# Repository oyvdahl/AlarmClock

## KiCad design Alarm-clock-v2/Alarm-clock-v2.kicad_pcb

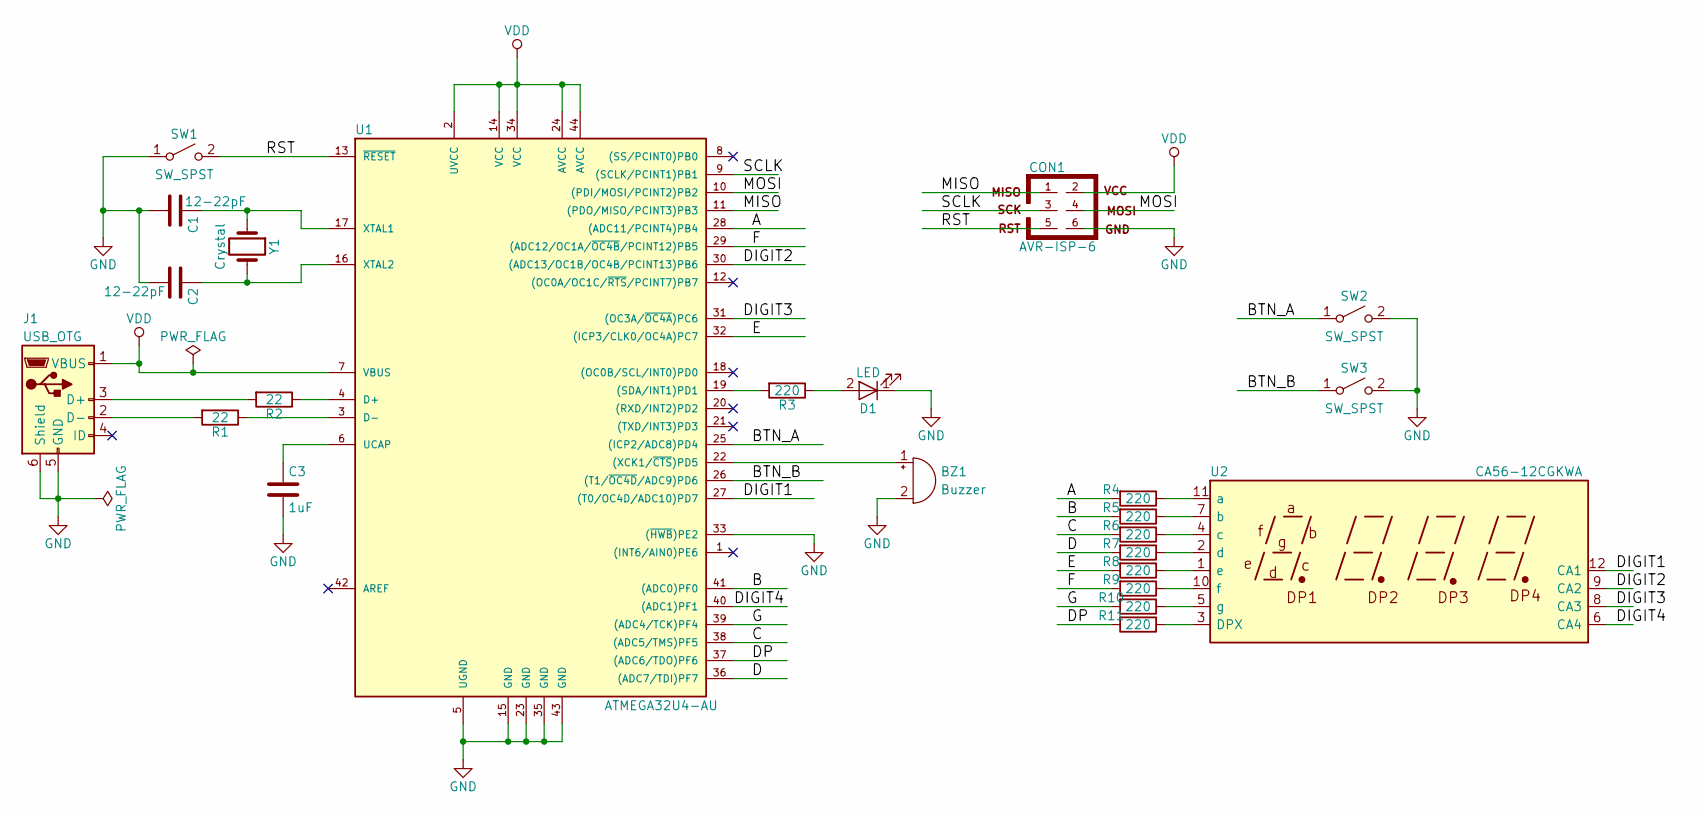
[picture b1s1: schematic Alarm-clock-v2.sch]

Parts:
BZ1: Buzzer; BUZZER
C1, C2: 12-22pF; C_0805
C3: 1uF; C_1206
CON1: AVR-ISP-6; Pin_Header_Straight_2x03_Pitch2.54mm_SMD
D1: LED; LED_1206
J1: USB_OTG; USB_Micro-B_Molex_47346-0001
R1, R2: 22; R_0805
R3, R4, R5, R6, R7, R8, R9, R10, R11: 220; R_0805
SW1, SW2, SW3: SW_SPST; SW_PUSH_6mm
U1: ATMEGA32U4-AU; TQFP-44_10x10mm_Pitch0.8mm
U2: CA56-12CGKWA
Y1: Crystal; Crystal_SMD_HC49-SD_HandSoldering

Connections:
/A: R4.2, U1.28 ((ADC11/PCINT4)PB4)
/B: R5.2, U1.41 ((ADC0)PF0)
/BTN_A: SW2.1 (A), U1.25 ((ICP2/ADC8)PD4)
/BTN_B: SW3.1 (A), U1.26 ((T1/~OC4D~/ADC9)PD6)
/C: R6.2, U1.38 ((ADC5/TMS)PF5)
/D: R7.2, U1.36 ((ADC7/TDI)PF7)
/DIGIT1: U1.27 ((T0/OC4D/ADC10)PD7), U2.12 (CA1)
/DIGIT2: U1.30 ((ADC13/OC1B/OC4B/PCINT13)PB6), U2.9 (CA2)
/DIGIT3: U1.31 ((OC3A/~OC4A~)PC6), U2.8 (CA3)
/DIGIT4: U1.40 ((ADC1)PF1), U2.6 (CA4)
/DP: R11.2, U1.37 ((ADC6/TDO)PF6)
/E: R8.2, U1.32 ((ICP3/CLK0/OC4A)PC7)
/F: R9.2, U1.29 ((ADC12/OC1A/~OC4B~/PCINT12)PB5)
/G: R10.2, U1.39 ((ADC4/TCK)PF4)
/MISO: CON1.1, U1.11 ((PDO/MISO/PCINT3)PB3)
/MOSI: CON1.4, U1.10 ((PDI/MOSI/PCINT2)PB2)
/RST: CON1.5, SW1.2 (B), U1.13 (~RESET~)
/SCLK: CON1.3, U1.9 ((SCLK/PCINT1)PB1)
GND: BZ1.2 (+), C1.2, C2.2, C3.2, CON1.6, D1.1 (K), J1.5 (GND), J1.6 (Shield), SW1.1 (A), SW2.2 (B), SW3.2 (B), U1.5 (UGND), U1.15 (GND), U1.23 (GND), U1.33 ((~HWB~)PE2), U1.35 (GND), U1.43 (GND)
unnamed: BZ1.1 (-), U1.22 ((XCK1/~CTS~)PD5)
unnamed: C1.1, U1.17 (XTAL1), Y1.1
unnamed: C2.1, U1.16 (XTAL2), Y1.2
unnamed: C3.1, U1.6 (UCAP)
unnamed: D1.2 (A), R3.1
unnamed: J1.2 (D-), R1.2
unnamed: J1.3 (D+), R2.2
unnamed: R1.1, U1.3 (D-)
unnamed: R2.1, U1.4 (D+)
unnamed: R3.2, U1.19 ((SDA/INT1)PD1)
unnamed: R4.1, U2.11 (a)
unnamed: R5.1, U2.7 (b)
unnamed: R6.1, U2.4 (c)
unnamed: R7.1, U2.2 (d)
unnamed: R8.1, U2.1 (e)
unnamed: R9.1, U2.10 (f)
unnamed: R10.1, U2.5 (g)
unnamed: R11.1, U2.3 (DPX)
VDD: CON1.2, J1.1 (VBUS), U1.2 (UVCC), U1.7 (VBUS), U1.14 (VCC), U1.24 (AVCC), U1.34 (VCC), U1.44 (AVCC)

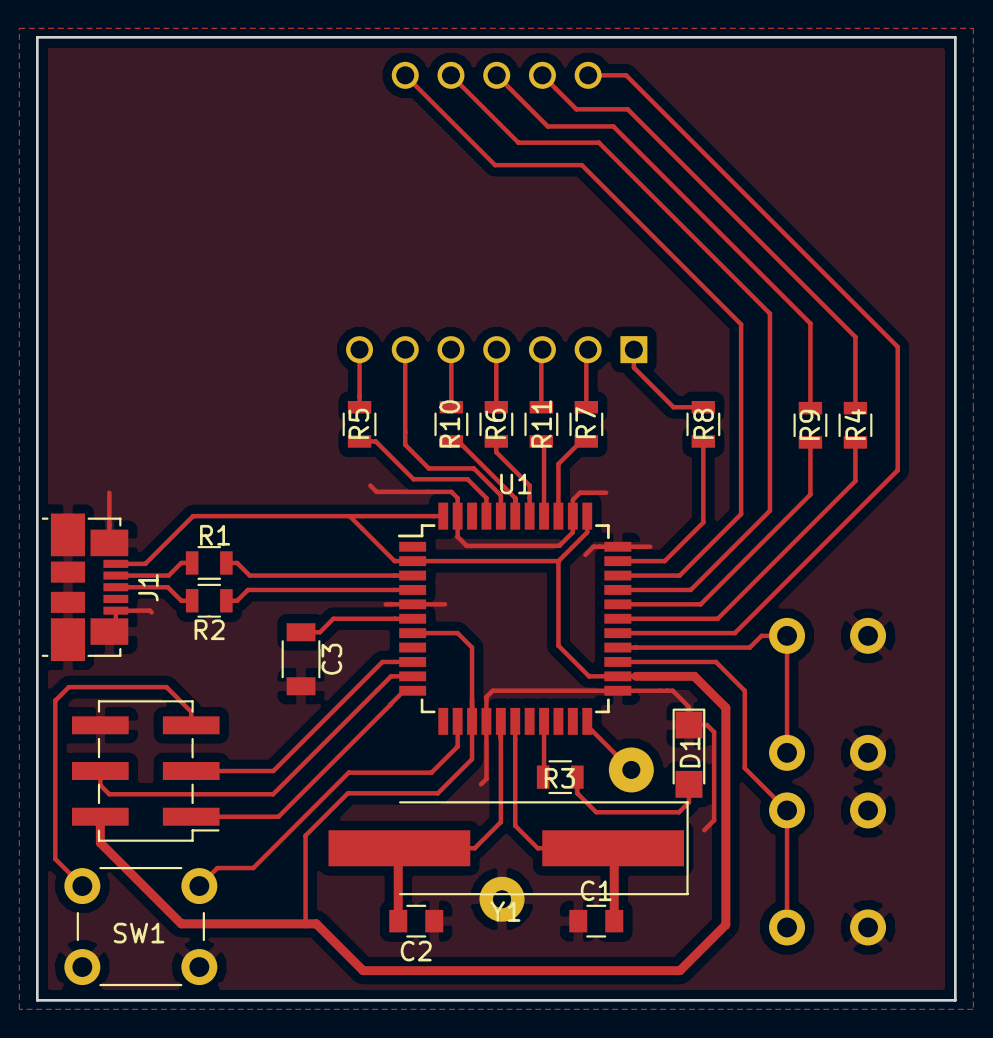
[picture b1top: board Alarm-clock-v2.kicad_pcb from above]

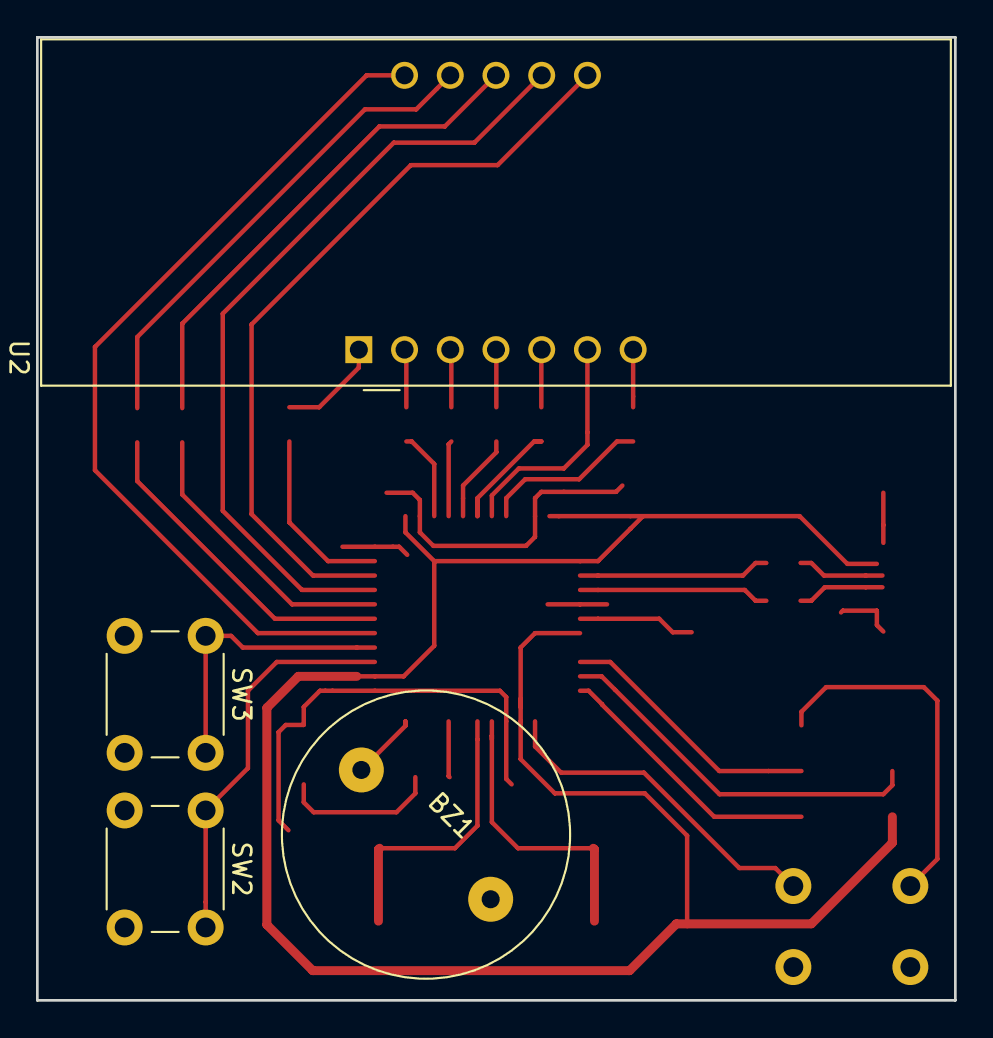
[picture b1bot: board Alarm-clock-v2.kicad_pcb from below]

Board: 2 copper layers, 51.0 x 53.5 mm, 24 parts (4 on the bottom side), 38 nets.

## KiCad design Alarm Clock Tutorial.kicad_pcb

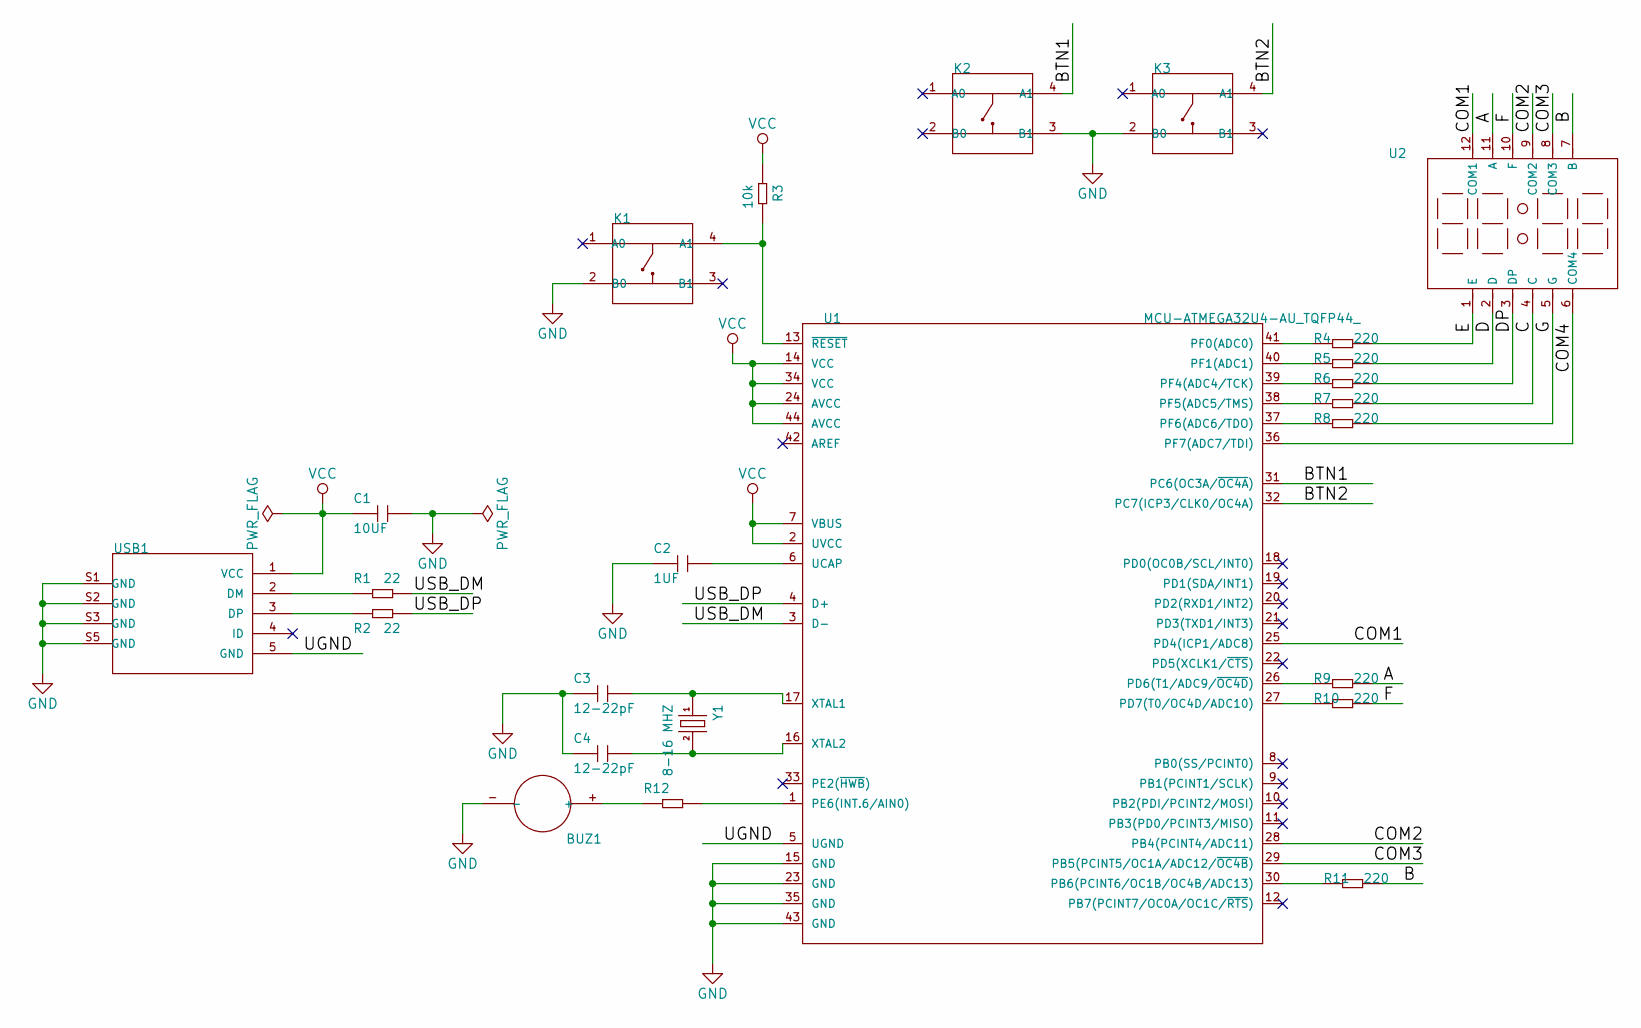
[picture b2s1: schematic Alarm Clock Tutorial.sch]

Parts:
BUZ1: DIP-BUZZER-3V_KS-12065D03YA_; BZ2-7.6-D12.0XH6.5MM; MPN KS-12065D03YA
C1: 10UF; C1206; MPN CC1206KKX5R8BB106
C2: 1UF; C0805; MPN CC0805KKX7R8BB105
C3, C4: 12-22pF; CERAMIC-2.54
K1, K2, K3: DIP-SWITCH-TACTILE-SPST-NO_TS-1109_4P-D6.0MM_; SW4-6.0X6.0X5.0MM
R1, R2: 22; R0805; MPN RC0805JR-0722RL
R3: 10k; R0402; MPN RC0402FR-0710KL
R4, R5, R6, R7, R8, R9, R10, R11: 220; R0805; MPN RC0805JR-07220RL
R12: DIP-RES-100R-5%-1_4W_PR-D2.3XL6.5MM_; PR-D2.3XL6.5MM; MPN FHCFR-1_4W-101J
U1: MCU-ATMEGA32U4-AU_TQFP44_; TQFP44-0.8-9.6X9.6MM; MPN ATMEGA32U4
U2: LED-4-BETY-7-SEG_2X7P-30X14MM_; LCD12-2.54-30.0X14.0X7.3MM; MPN LDQ-N3606RI
USB1: MICRO-USB-SMD-B-_10118193-0001LF_; MICRO-USB5+6P-SMD-0.65-B; MPN 10118193-0001LF
Y1: 8-16 MHZ; HC49US

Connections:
/A: R9.2, U2.11 (A)
/B: R11.2, U2.7 (B)
/BTN1: K2.4 (A1), U1.31 (PC6(OC3A/~OC4A))
/BTN2: K3.4 (A1), U1.32 (PC7(ICP3/CLK0/OC4A))
/C: R7.2, U2.4 (C)
/COM1: U1.25 (PD4(ICP1/ADC8)), U2.12 (COM1)
/COM2: U1.28 (PB4(PCINT4/ADC11)), U2.9 (COM2)
/COM3: U1.29 (PB5(PCINT5/OC1A/ADC12/~OC4B)), U2.8 (COM3)
/COM4: U1.36 (PF7(ADC7/TDI)), U2.6 (COM4)
/D: R5.2, U2.2 (D)
/DP: R6.2, U2.3 (DP)
/E: R4.2, U2.1 (E)
/F: R10.2, U2.10 (F)
/G: R8.2, U2.5 (G)
/UGND: U1.5 (UGND), USB1.5 (GND)
/USB_DM: R1.2, U1.3 (D-)
/USB_DP: R2.2, U1.4 (D+)
GND: BUZ1.-, C1.2, C2.1, C3.1, C4.1, K1.2 (B0), K2.3 (B1), K3.2 (B0), U1.15 (GND), U1.23 (GND), U1.35 (GND), U1.43 (GND), USB1.S1 (GND), USB1.S2 (GND), USB1.S3 (GND), USB1.S4 (GND), USB1.S5 (GND), USB1.S6 (GND)
unnamed: BUZ1.+, R12.1
unnamed: C2.2, U1.6 (UCAP)
unnamed: C3.2, U1.17 (XTAL1), Y1.1
unnamed: C4.2, U1.16 (XTAL2), Y1.2
unnamed: K1.4 (A1), R3.2, U1.13 (~RESET)
unnamed: R1.1, USB1.2 (DM)
unnamed: R2.1, USB1.3 (DP)
unnamed: R4.1, U1.41 (PF0(ADC0))
unnamed: R5.1, U1.40 (PF1(ADC1))
unnamed: R6.1, U1.39 (PF4(ADC4/TCK))
unnamed: R7.1, U1.38 (PF5(ADC5/TMS))
unnamed: R8.1, U1.37 (PF6(ADC6/TDO))
unnamed: R9.1, U1.26 (PD6(T1/ADC9/~OC4D))
unnamed: R10.1, U1.27 (PD7(T0/OC4D/ADC10))
unnamed: R11.1, U1.30 (PB6(PCINT6/OC1B/OC4B/ADC13))
unnamed: R12.2, U1.1 (PE6(INT.6/AIN0))
VCC: C1.1, R3.1, U1.2 (UVCC), U1.7 (VBUS), U1.14 (VCC), U1.24 (AVCC), U1.34 (VCC), U1.44 (AVCC), USB1.1 (VCC)

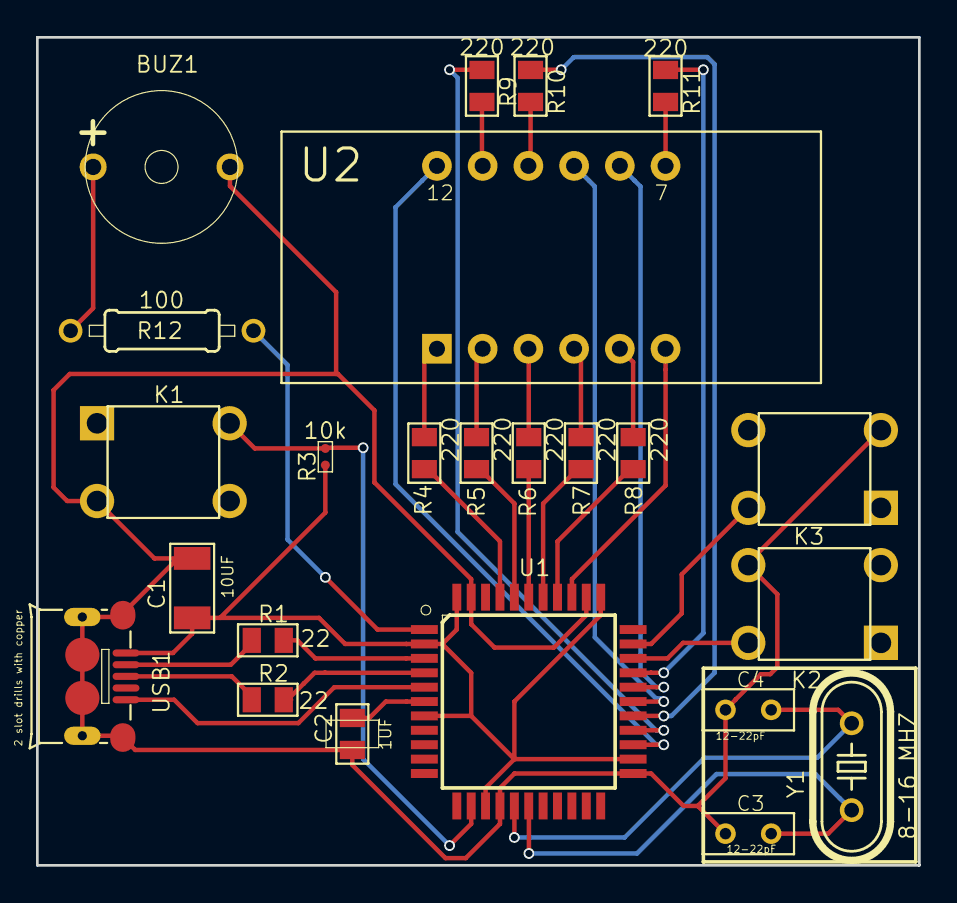
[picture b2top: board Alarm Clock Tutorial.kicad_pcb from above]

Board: 2 copper layers, 49.0 x 46.0 mm, 24 parts (0 on the bottom side), 35 nets.

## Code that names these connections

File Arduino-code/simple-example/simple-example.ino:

#include <avr/io.h>
#include <util/delay.h>
#include <avr/interrupt.h>



// Port B - Outputs
#define COM2 PB4
#define COM3 PB5
#define SEGMENT_B PB6

// Port D - Outputs
#define COM1 PD4
#define SEGMENT_A PD6
#define SEGMENT_F PD7

// Port F - Outputs
#define  COM4 PF7
#define  SEGMENT_C PF5
#define  SEGMENT_D PF1
#define  SEGMENT_E PF0
#define  SEGMENT_G PF6
#define  SEGMENT_DP PF4

// Port E - Outputs
#define BUZZER PE6

// Port C - Inputs
#define BTN_INPUT1 PC6
#define BTN_INPUT2 PC7

volatile int countdown_from_s = 15;
volatile int count = 0;
volatile int seconds = 0;
volatile int disp1_value = 9;
volatile int disp2_value = 8;
volatile int disp3_value = 7;
volatile int disp4_value = 6;
volatile int stop;





void setup() {
  // Setup outputs
  DDRB = ((1 << SEGMENT_B) | (1 << COM2) | (1 << COM3));
  DDRD = ((1 << SEGMENT_A) | (1 << SEGMENT_F) | (1 << COM1));
  DDRF = ((1 << SEGMENT_C) | (1 << SEGMENT_D) | (1 << SEGMENT_E) | (1 << SEGMENT_G) | (1 << SEGMENT_DP) | (1 << COM4));
  DDRE = (1 << BUZZER);
  

  // Disable buzzer
  enable_buzzer(false);

  //Enable the timer
  //enable_timer();

  // initialize timer1
  noInterrupts();           // disable all interrupts
  TCCR1A = 0;
  TCCR1B = 0;

  //TCNT1 = 34286;            // preload timer 65536-16MHz/256/2Hz
  TCNT1 = 49911;
  TCCR1B |= (1 << CS12) | (1 << CS10);    // 1024 prescaler
  TIMSK1 |= (1 << TOIE1);   // enable timer overflow interrupt
  interrupts();             // enable all interrupts
}

void loop() {


  ////////////////////
  // UPDATE DISPLAY //
  ////////////////////

  set_digit(disp1_value);
  set_segDP(false);
  enable_digit_x(1);
  _delay_ms(5);

  set_digit(disp2_value);
  set_segDP(true);
  enable_digit_x(2);
  _delay_ms(5);

  set_digit(disp3_value);
  set_segDP(false);
  enable_digit_x(3);
  _delay_ms(5);

  set_digit(disp4_value);
  set_segDP(false);
  enable_digit_x(4);
  _delay_ms(5);

}




void enable_timer() {

  TCCR1B |= 1 << WGM12;
  TCCR1B |= 1 << CS12;
  OCR1A = 300;
  TIMSK1 |= 1 << OCIE1A;


  sei();                               // enable all interrupts

}


void enable_buzzer(int enable) {
  if (enable) {
    PORTE |= (1 << PE6);
  } else {
    PORTE &= ~(1 << PE6);
  }
}

//Pull COM1 low to enable
void enable_digit_1(int enable)
{
  if (!enable) {
    PORTD |= (1 << PD4);
  } else {
    PORTD &= ~(1 << PD4);
  }
}

//Pull COM2 low to enable
void enable_digit_2(int enable)
{
  if (!enable) {
    PORTB |= (1 << PB4);
  } else {
    PORTB &= ~(1 << PB4);
  }
}

//Pull COM3 low to enable
void enable_digit_3(int enable)
{
  if (!enable) {
    PORTB |= (1 << PB5);
  } else {
    PORTB &= ~(1 << PB5);
  }
}

//Pull COM4 low to enable
void enable_digit_4(int enable)
{
  if (!enable) {
    PORTF |= (1 << PF7);
  } else {
    PORTF &= ~(1 << PF7);
  }
}

void set_segA(int enable) {
  if (enable) {
    PORTD |= (1 << PD6);
  } else {
    PORTD &= ~(1 << PD6);
  }
}

void set_segB(int enable) {
  if (enable) {
    PORTB |= (1 << PB6);
  } else {
    PORTB &= ~(1 << PB6);
  }
}

void set_segC(int enable) {
  if (enable) {
    PORTF |= (1 << PF5);
  } else {
    PORTF &= ~(1 << PF5);
  }
}

void set_segD(int enable) {
  if (enable) {
    PORTF |= (1 << PF1);
  } else {
    PORTF &= ~(1 << PF1);
  }
}

void set_segE(int enable) {
  if (enable) {
    PORTF |= (1 << PF0);
  } else {
    PORTF &= ~(1 << PF0);
  }
}

void set_segF(int enable) {
  if (enable) {
    PORTD |= (1 << PD7);
  } else {
    PORTD &= ~(1 << PD7);
  }
}

void set_segG(int enable) {
  if (enable) {
    PORTF |= (1 << PF6);
  } else {
    PORTF &= ~(1 << PF6);
  }
}

void set_segDP(int enable) {
  if (enable) {
    PORTF |= (1 << PF4);
  } else {
    PORTF &= ~(1 << PF4);
  }
}

void enable_digit_x(int digit)
{
  switch (digit)
  {
    case 1:
      enable_digit_1(true);
      enable_digit_2(false);
      enable_digit_3(false);
      enable_digit_4(false);
      break;
    case 2:
      enable_digit_1(false);
      enable_digit_2(true);
      enable_digit_3(false);
      enable_digit_4(false);
      break;
    case 3:
      enable_digit_1(false);
      enable_digit_2(false);
      enable_digit_3(true);
      enable_digit_4(false);
      break;
    case 4:
      enable_digit_1(false);
      enable_digit_2(false);
      enable_digit_3(false);
      enable_digit_4(true);
      break;

  }
}

void set_digit(int number)
{

  // The following switch statement turns on the correct segments for the number to show
  switch (number) {

    case 0 :
      set_segA(true);
      set_segB(true);
      set_segC(true);
      set_segD(true);
      set_segE(true);
      set_segF(true);
      set_segG(false);
      break;

    case 1  :
      set_segA(false);
      set_segB(true);
      set_segC(true);
      set_segD(false);
      set_segE(false);
      set_segF(false);
      set_segG(false);
      break;

    case 2  :
      set_segA(true);
      set_segB(true);
      set_segC(false);
      set_segD(true);
      set_segE(true);
      set_segF(false);
      set_segG(true);
      break;

    case 3  :
      set_segA(true);
      set_segB(true);
      set_segC(true);
      set_segD(true);
      set_segE(false);
      set_segF(false);
      set_segG(true);
      break;

    case 4  :
      set_segA(false);
      set_segB(true);
      set_segC(true);
      set_segD(false);
      set_segE(false);
      set_segF(true);
      set_segG(true);
      break;

    case 5 :
      set_segA(true);
      set_segB(false);
      set_segC(true);
      set_segD(true);
      set_segE(false);
      set_segF(true);
      set_segG(true);
      break;

    case 6 :
      set_segA(true);
      set_segB(false);
      set_segC(true);
      set_segD(true);
      set_segE(true);
      set_segF(true);
      set_segG(true);
      break;

    case 7 :
      set_segA(true);
      set_segB(true);
      set_segC(true);
      set_segD(false);
      set_segE(false);
      set_segF(false);
      set_segG(false);
      break;

    case 8 :
      set_segA(true);
      set_segB(true);
      set_segC(true);
      set_segD(true);
      set_segE(true);
      set_segF(true);
      set_segG(true);
      break;

    case 9 :
      set_segA(true);
      set_segB(true);
      set_segC(true);
      set_segD(true);
      set_segE(false);
      set_segF(true);
      set_segG(true);
      break;

    // sets E for Error
    default :
      set_segA(true);
      set_segB(false);
      set_segC(false);
      set_segD(true);
      set_segE(true);
      set_segF(true);
      set_segG(true);
  }


}




ISR(TIMER1_OVF_vect)        // interrupt service routine that wraps a user defined function supplied by attachInterrupt
{
  int seconds_without_minutes, minutes_without_seconds, disp_s, stop_cd;
  //TCNT1 = 34286;            // preload timer
  TCNT1 = 49911;
  seconds++;

  // Display time left from countdown:
  disp_s = countdown_from_s - seconds;

  if (disp_s == 0) {
    stop_cd = true;

    while (1) {
      enable_buzzer(true);
      _delay_ms(200);
      enable_buzzer(false);
      _delay_ms(100);
    }
  }

  // Separate the digits:
  seconds_without_minutes = disp_s % 60;
  disp4_value =  seconds_without_minutes % 10;
  disp3_value =  seconds_without_minutes / 10;

  minutes_without_seconds = disp_s / 60;
  disp2_value = minutes_without_seconds % 10;
  disp1_value = minutes_without_seconds / 10;
}

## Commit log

2018-01-05 Schematics almost done
2018-01-05 Added gitignore
2018-01-05 Removed DS_Store
2018-01-07 First version fully routed
2018-01-08 This version was ordered from Seeed Studio
2018-01-17 Latest
2018-01-25 Updated part number for 7-segment
2018-01-30 Creating new version using standard kicad libs
2018-01-30 Created bare minimum USB version
2018-01-30 Added 7-segment component in lib
2018-02-06 Updated component values on board
2018-02-06 Added first arduino code example
2018-03-01 New version of Alarm-clock added
2018-03-02 Added buzzer
